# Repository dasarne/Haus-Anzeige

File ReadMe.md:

Dieses Projekt soll eine Anzeige für IoT-Daten erstellen. Basis ist ein 3,2" TFT Touchscreen Display Modul ILI9341 240x320, das über einen ESP32 angesteuert wird.

* Der Ordner `Haus-Anzeige-Projekt` beinhaltet ein PlatformIO-Projekt das auf den ESP32 geflashet werden kann.
* Der `KICad`-Ordner beinhaltet das Platinen-Layout.
* Und der Ordner `Sqareline-Projekt` beinhaltet die UI.

This project is intended to create a display for IoT data. The basis is a 3.2" TFT touchscreen display module ILI9341 240x320, which is controlled via an ESP32.

* The `House-Display-Project` folder contains a PlatformIO project that can be flashed to the ESP32.
* The `KICad` folder contains the board layout.
* And the `Sqareline-Project` folder contains the UI.

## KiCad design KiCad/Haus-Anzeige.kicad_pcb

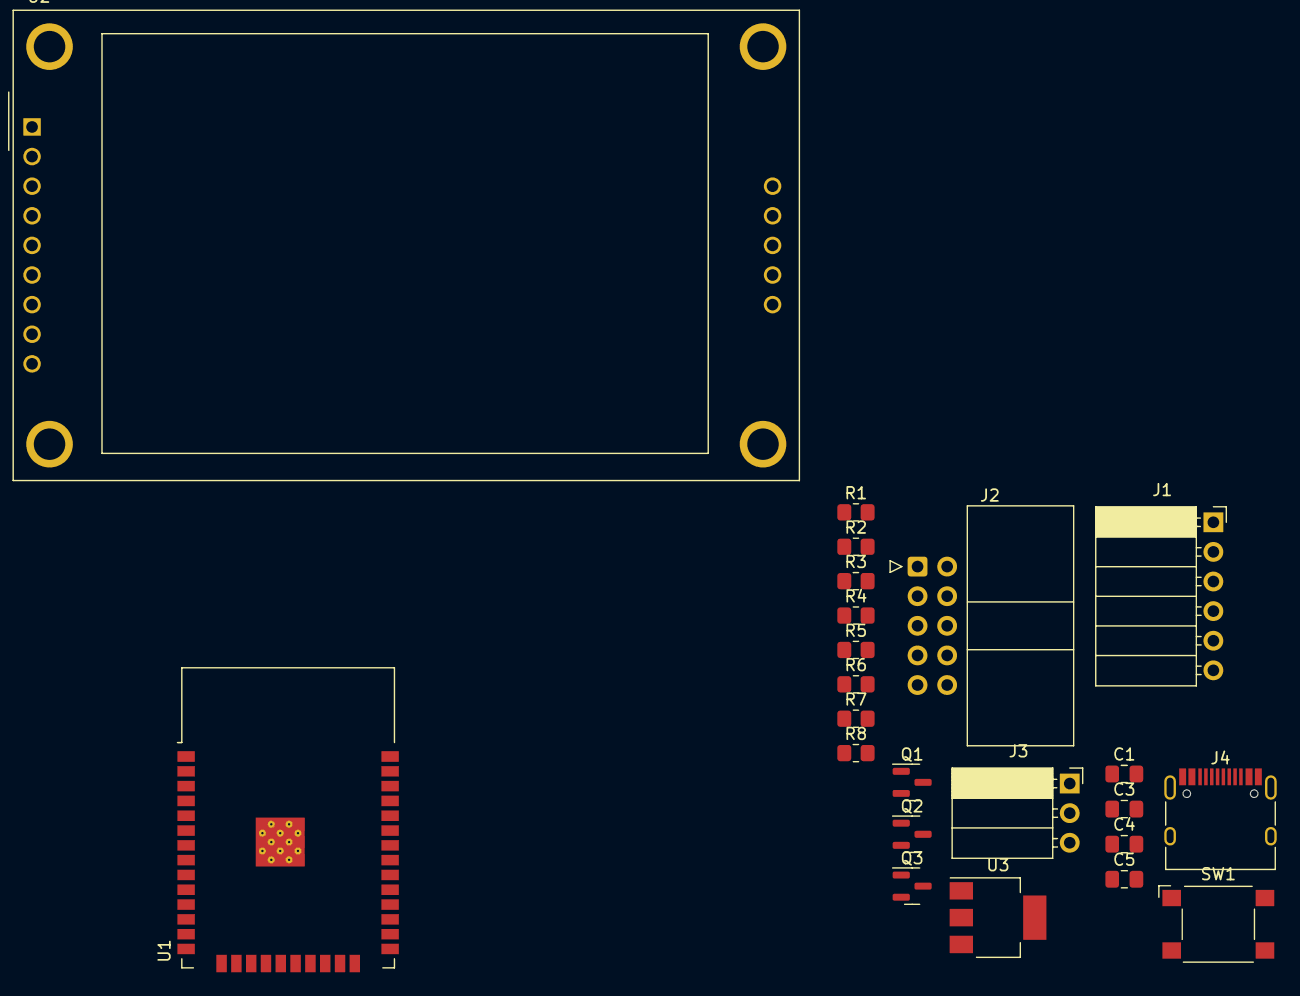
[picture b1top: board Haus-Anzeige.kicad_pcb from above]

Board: 2 copper layers, 23 parts (0 on the bottom side), 22 nets, no tracks yet.

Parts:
C1, C3, C4, C5: 1uF; C_0805_2012Metric_Pad1.18x1.45mm_HandSolder
J1: Prog-Socket; PinSocket_1x06_P2.54mm_Horizontal
J2: JTAG; IDC-Header_2x05_P2.54mm_Horizontal
J3: Analog; PinSocket_1x03_P2.54mm_Horizontal
J4: USB_C_Receptacle_USB2.0; USB_C_Receptacle_WUERTH_TYPE-C-12
Q1: BC857; SOT-23
Q2, Q3: BC847; SOT-23
R1, R2, R4, R5: 10k; R_0805_2012Metric_Pad1.20x1.40mm_HandSolder
R3: 1k; R_0805_2012Metric_Pad1.20x1.40mm_HandSolder
R6, R7: 5k1; R_0805_2012Metric_Pad1.20x1.40mm_HandSolder
R8: 100R; R_0805_2012Metric_Pad1.20x1.40mm_HandSolder
SW1: SW_Push; SW_SPST_Omron_B3FS-100xP
U1: ESP32-WROOM-32
U2: CR2013-MI2120
U3: AMS1117-3.3; SOT-223-3_TabPin2

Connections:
+3.3V: C3.1, C5.1, J1.3, J2.1, R1.1, R2.1, R8.1, U1.2 (VDD), U3.2 (VO)
/BOOT: Q2.3 (C), R2.2, U1.25 (IO0)
/DTR: J1.6, Q2.2 (E), R5.1
/EN: Q3.3 (C), R1.2, SW1.2, U1.3 (EN)
/L: J3.3, U1.10 (IO25)
/R: J3.1, U1.11 (IO26)
/RTS: J1.2, Q3.2 (E), R4.1
/Rx: J1.5, U1.34 (RXD0/IO3)
/TCK: J2.4, U1.16 (IO13)
/TDI: J2.8, U1.14 (IO12)
/TDO: J2.6, U1.23 (IO15)
/TMS: J2.2, U1.13 (IO14)
/Tx: J1.4, U1.35 (TXD0/IO1)
/~LED: R3.2, U1.12 (IO27)
GND: C1.1, C1.2, C3.2, C4.2, C5.2, J1.1, J2.3, J2.5, J2.7, J2.9, J3.2, J4.A1 (GND), J4.A12 (GND), J4.B1 (GND), J4.B12 (GND), R6.2, R7.2, SW1.1, U1.1 (GND), U1.15 (GND), U1.38 (GND), U1.39 (GND), U3.1 (GND)
unnamed: J4.A5 (CC1), R7.1
unnamed: J4.B5 (CC2), R6.1
unnamed: Q1.2 (B), R3.1
unnamed: Q1.3 (E), R8.2
unnamed: Q2.1 (B), R4.2
unnamed: Q3.1 (B), R5.2
unnamed: C4.1, J4.A4 (VBUS), J4.A9 (VBUS), J4.B4 (VBUS), J4.B9 (VBUS), U3.3 (VI)

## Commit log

2023-11-23 Initial
2023-11-23 ReadMe hinzugefügt
